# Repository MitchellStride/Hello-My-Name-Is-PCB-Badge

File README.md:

# 🎉 "Hello My Name Is" PCB Badge

This **#Badgelife** PCB was created to test some circuits for future art PCBs.  
It also served as a small project to bring to local hardware meetups. Partial assembly was done at JLCPCB.

## ⚡ Example GIF

---

## 🔧 Features
- Powered by 2× AA Batteries
- Highly compatible with JLCPCB's basic SMT parts
- Raspberry Pi RP2040 microcontroller with dual-core ARM Cortex-M0+
- OLED Screen, RGB LEDs, Buttons
- SAO Connector

---

## ⚠️ v1 Issues
I rushed this project a lot. The schematic was done in a few nights, layout and routing in a few hours with no review. This PCB has a few mistakes. Not planning another spin, but leaving this list here:  

<details>
<summary>Click to expand v1 Issues</summary>

- I saw someone else's design online using an RGB LED running at 3.3V (below spec). I tried to replicate it, and the LEDs were very flaky and worked intermittently. Experiment failed 😢.  
- AA boost converter not yet tested; currently using USB power only.

</details>

---

## 📝 v2 Wishlist
<details>
<summary>Click to expand v2 Todo</summary>

- User LED + Power LED  
- ON/OFF silk on switch  
- Buzzer would be fun  
- 5.1k USB CC1/CC2  
- Planes on battery terminals to prevent lifting  
- Use RPi boost for AA supply instead of boost converter  
  - It’s nice to have 5V for LEDs  
- SAO connector is too big for this little PCB  
- GND probe clip stuffing option  
- Level shifter for RGB LEDs  

</details>

---

*Missing front buttons on this test PCB*

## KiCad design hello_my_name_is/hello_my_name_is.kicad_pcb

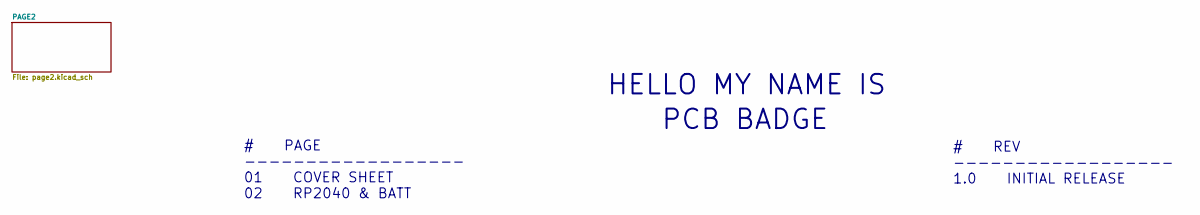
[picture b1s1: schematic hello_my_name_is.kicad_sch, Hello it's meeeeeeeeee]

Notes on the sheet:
# REV ------------------ 1.0 INITIAL RELEASE
HELLO MY NAME IS
PCB BADGE
# PAGE ------------------ 01 COVER SHEET 02 RP2040 & BATT

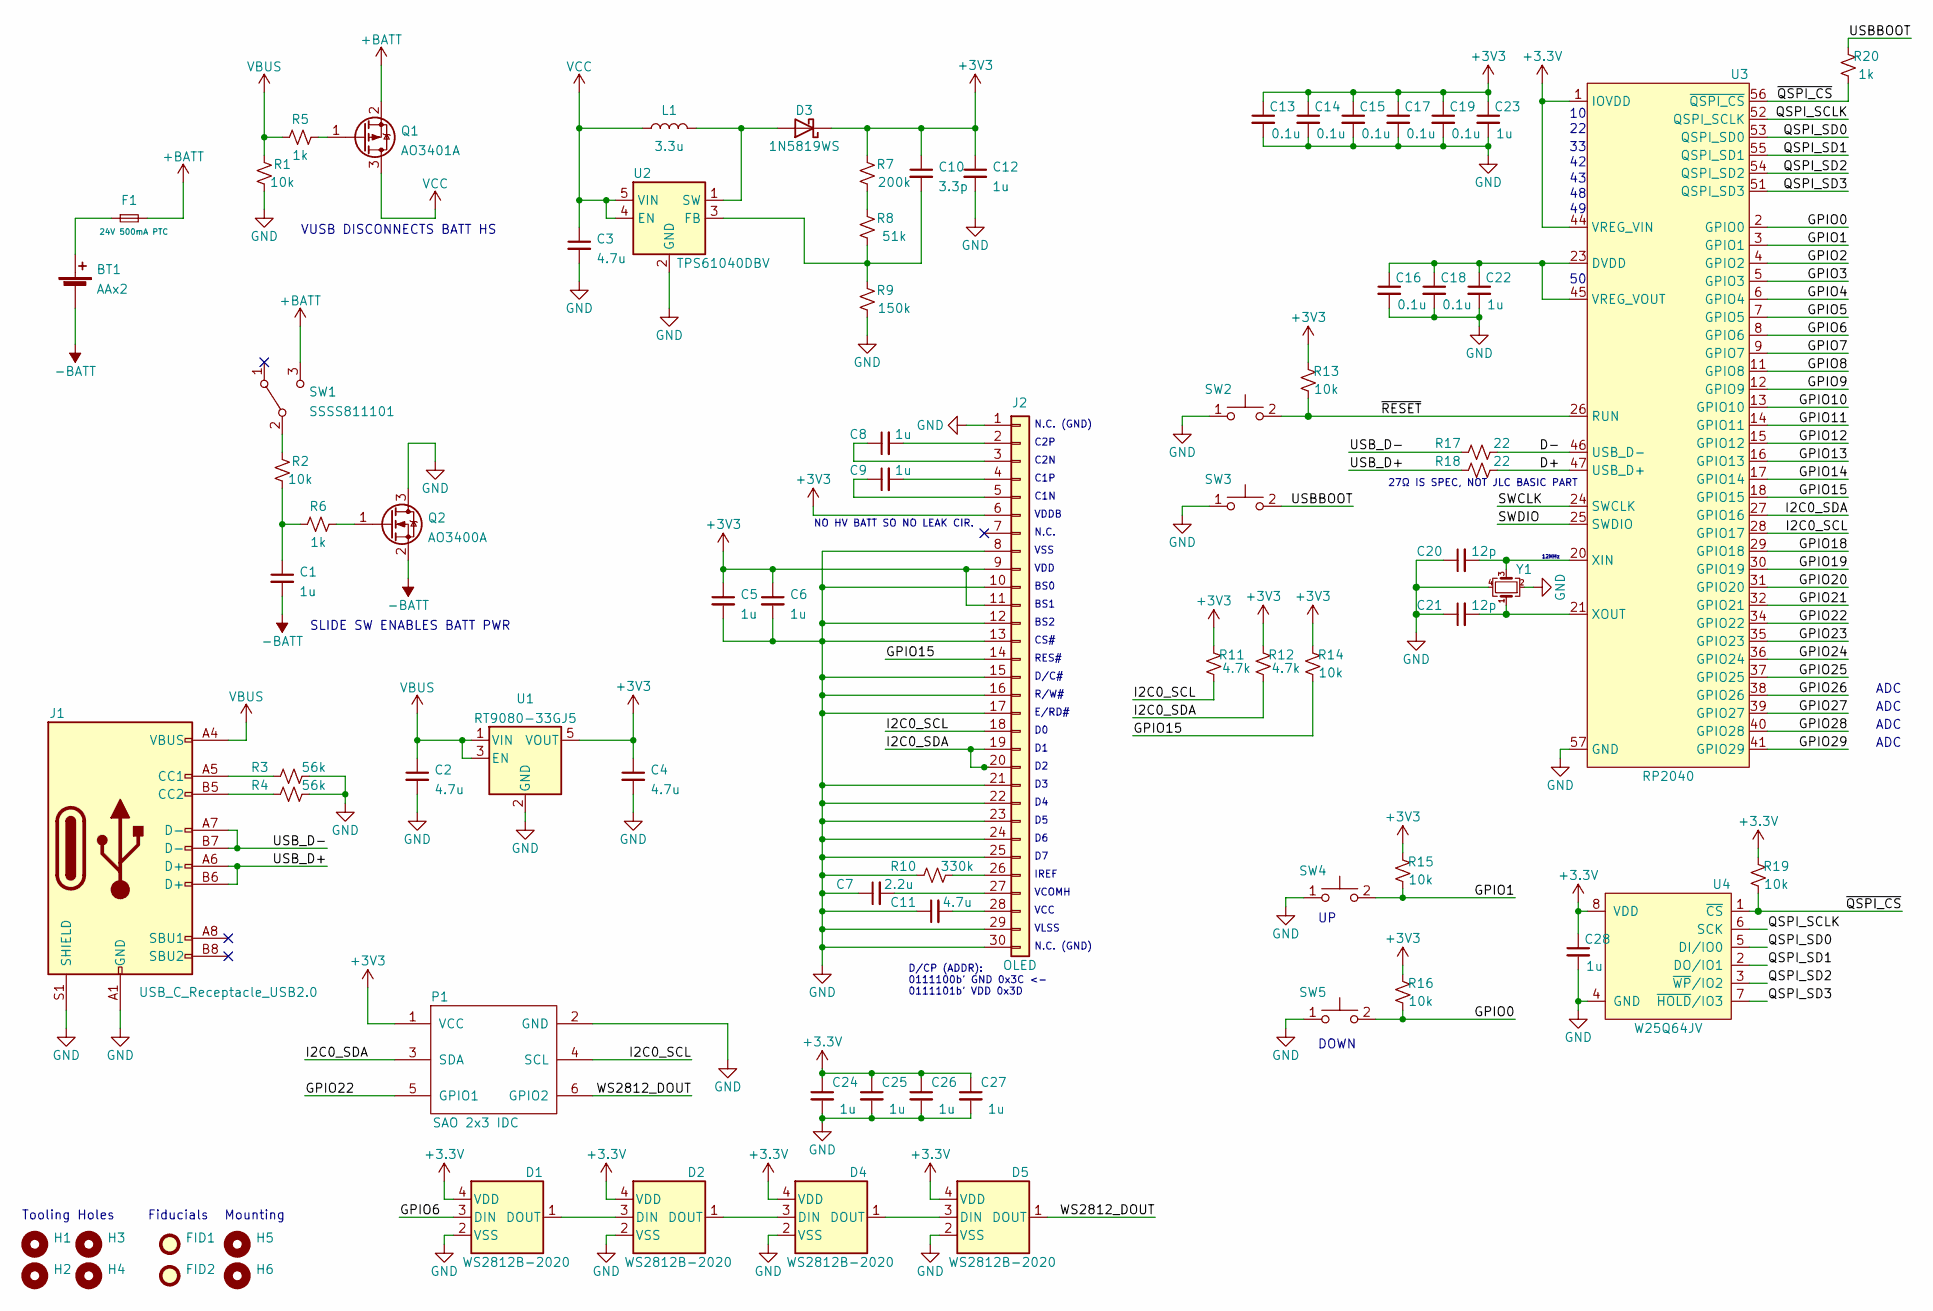
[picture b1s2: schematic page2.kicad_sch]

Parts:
BT1: AAx2; BatteryHolder_MPD_BC2AAPC_2xAA_mod-SMD; digi BC2AAPC
C1, C5, C6, C8, C9, C12, C22, C23, C24, C25, C26, C27, C28: 1u; C_0402_1005Metric; lcsc C52923
C2, C3, C4, C11: 4.7u; C_0402_1005Metric; lcsc C23733
C7: 2.2u; C_0402_1005Metric; lcsc C12530
C10: 3.3p; C_0402_1005Metric; lcsc C1565
C13, C14, C15, C16, C17, C18, C19: 0.1u; C_0402_1005Metric; lcsc C1525
C20, C21: 12p; C_0402_1005Metric; lcsc C1547
D1, D2, D4, D5: WS2812B-2020; lcsc C965555
D3: 1N5819WS; D_SOD-323; lcsc C191023
F1: 24V 500mA PTC; Fuse_0805_2012Metric; lcsc C910822
FID1, FID2: Fiducial; Fiducial_1mm_Mask2mm
H1, H2, H3, H4: Tooling_Hole_JLC; JLC_Tooling_Hole
H5, H6: Tooling_Hole_JLC; MountingHole_3.2mm_M3
J1: USB_C_Receptacle_USB2.0; USB-C-16p; lcsc C167321
J2: OLED; OLED-128O064D; lcsc C2890596
L1: 3.3u; L_Bourns-SRN4018; lcsc C431259
P1: SAO 2x3 IDC; Badgelife-SAOv169-BADGE-2x3; lcsc C11214
Q1: AO3401A; SOT-23; lcsc C15127
Q2: AO3400A; SOT-23; lcsc C20917
R1, R2, R13, R14, R15, R16, R19: 10k; R_0402_1005Metric; lcsc C25744
R3, R4: 56k; R_0402_1005Metric; lcsc C25796
R5, R6, R20: 1k; R_0402_1005Metric; lcsc C11702
R7: 200k; R_0402_1005Metric; lcsc C25764
R8: 51k; R_0402_1005Metric; lcsc C25794
R9: 150k; R_0402_1005Metric; lcsc C25755
R10: 330k; R_0402_1005Metric; lcsc C25778
R11, R12: 4.7k; R_0402_1005Metric; lcsc C25900
R17, R18: 22; R_0402_1005Metric; lcsc C25092
SW1: SSSS811101; lcsc C109335
SW2, SW3, SW4, SW5: TS-1187A-B-A-B; SW_SPST_TL3342; lcsc C318884
U1: RT9080-33GJ5; SOT-23-5; lcsc C841192
U2: TPS61040DBV; SOT-23-5; lcsc C7722
U3: RP2040; QFN-56_EP_7x7_Pitch0.4mm; lcsc C2040
U4: W25Q64JV; SOIC-8W_5.3x5.3mm_P1.27mm; lcsc C179171
Y1: XYDBPCNANF-12MHZ; Crystal_SMD_2520-4Pin_2.5x2.0mm; lcsc C521567

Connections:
+BATT: F1.2, Q1.2 (S), SW1.3 (C)
-BATT: BT1.2 (-), C1.2, Q2.2 (S)
/PAGE2/D+: R18.2, U3.47 (USB_D+)
/PAGE2/D-: R17.2, U3.46 (USB_D-)
/PAGE2/GPIO0: R16.2, SW5.2, U3.2 (GPIO0)
/PAGE2/GPIO1: R15.2, SW4.2, U3.3 (GPIO1)
/PAGE2/GPIO2: U3.4 (GPIO2)
/PAGE2/GPIO3: U3.5 (GPIO3)
/PAGE2/GPIO4: U3.6 (GPIO4)
/PAGE2/GPIO5: U3.7 (GPIO5)
/PAGE2/GPIO6: D1.3 (DIN), U3.8 (GPIO6)
/PAGE2/GPIO7: U3.9 (GPIO7)
/PAGE2/GPIO8: U3.11 (GPIO8)
/PAGE2/GPIO9: U3.12 (GPIO9)
/PAGE2/GPIO10: U3.13 (GPIO10)
/PAGE2/GPIO11: U3.14 (GPIO11)
/PAGE2/GPIO12: U3.15 (GPIO12)
/PAGE2/GPIO13: U3.16 (GPIO13)
/PAGE2/GPIO14: U3.17 (GPIO14)
/PAGE2/GPIO15: J2.14, R14.2, U3.18 (GPIO15)
/PAGE2/GPIO18: U3.29 (GPIO18)
/PAGE2/GPIO19: U3.30 (GPIO19)
/PAGE2/GPIO20: U3.31 (GPIO20)
/PAGE2/GPIO21: U3.32 (GPIO21)
/PAGE2/GPIO22: P1.5 (GPIO1), U3.34 (GPIO22)
/PAGE2/GPIO23: U3.35 (GPIO23)
/PAGE2/GPIO24: U3.36 (GPIO24)
/PAGE2/GPIO25: U3.37 (GPIO25)
/PAGE2/GPIO26: U3.38 (GPIO26)
/PAGE2/GPIO27: U3.39 (GPIO27)
/PAGE2/GPIO28: U3.40 (GPIO28)
/PAGE2/GPIO29: U3.41 (GPIO29)
/PAGE2/I2C0_SCL: J2.18, P1.4 (SCL), R11.2, U3.28 (GPIO17)
/PAGE2/I2C0_SDA: J2.19, J2.20, P1.3 (SDA), R12.2, U3.27 (GPIO16)
/PAGE2/QSPI_SCLK: U3.52 (QSPI_SCLK), U4.6 (SCK)
/PAGE2/QSPI_SD0: U3.53 (QSPI_SD0), U4.5 (DI/IO0)
/PAGE2/QSPI_SD1: U3.55 (QSPI_SD1), U4.2 (DO/IO1)
/PAGE2/QSPI_SD2: U3.54 (QSPI_SD2), U4.3 (~WP/IO2)
/PAGE2/QSPI_SD3: U3.51 (QSPI_SD3), U4.7 (~HOLD/IO3)
/PAGE2/SWCLK: U3.24 (SWCLK)
/PAGE2/SWDIO: U3.25 (SWDIO)
/PAGE2/USBBOOT: R20.1, SW3.2
/PAGE2/USB_D+: J1.A6 (D+), J1.B6 (D+), R18.1
/PAGE2/USB_D-: J1.A7 (D-), J1.B7 (D-), R17.1
/PAGE2/WS2812_DOUT: D5.1 (DOUT), P1.6 (GPIO2)
/PAGE2/~QSPI_CS: R19.2, R20.2, U3.56 (~QSPI_CS), U4.1 (~CS)
/PAGE2/~RESET: R13.2, SW2.2, U3.26 (RUN)
GND: C2.2, C3.2, C4.2, C5.2, C6.2, C7.1, C11.1, C12.2, C13.2, C14.2, C15.2, C16.2, C17.2, C18.2, C19.2, C20.1, C21.1, C22.2, C23.2, C24.2, C25.2, C26.2, C27.2, C28.2, D1.2 (VSS), D2.2 (VSS), D4.2 (VSS), D5.2 (VSS), J1.A1 (GND), J1.A12 (GND), J1.B1 (GND), J1.B12 (GND), J1.S1 (SHIELD), J2.1, J2.8, J2.10, J2.12, J2.13, J2.15, J2.16, J2.17, J2.21, J2.22, J2.23, J2.24, J2.25, J2.29, J2.30, P1.2 (GND), Q2.3 (D), R1.2, R3.2, R4.2, R9.2, R10.1, SW2.1, SW3.1, SW4.1, SW5.1, U1.2 (GND), U2.2 (GND), U3.19 (TESTEN), U3.57 (GND), U4.4 (GND), U4.9 (GND), Y1.2, Y1.4
unnamed: BT1.1 (+), F1.1
unnamed: C1.1, R2.2, R6.1
unnamed: C7.2, J2.27
unnamed: C8.1, J2.3
unnamed: C8.2, J2.2
unnamed: C9.1, J2.5
unnamed: C9.2, J2.4
unnamed: C10.2, R8.2, R9.1, U2.3 (FB)
unnamed: C11.2, J2.28
unnamed: C16.1, C18.1, C22.1, U3.23 (DVDD), U3.45 (VREG_VOUT), U3.50 (DVDD)
unnamed: C20.2, U3.20 (XIN), Y1.3
unnamed: C21.2, U3.21 (XOUT), Y1.1
unnamed: D1.1 (DOUT), D2.3 (DIN)
unnamed: D2.1 (DOUT), D4.3 (DIN)
unnamed: D3.2 (A), L1.2, U2.1 (SW)
unnamed: D4.1 (DOUT), D5.3 (DIN)
unnamed: J1.A5 (CC1), R3.1
unnamed: J1.B5 (CC2), R4.1
unnamed: J2.26, R10.2
unnamed: Q1.1 (G), R5.2
unnamed: Q2.1 (G), R6.2
unnamed: R2.1, SW1.2 (B)
unnamed: R7.2, R8.1
VBUS: C2.1, J1.A4 (VBUS), J1.A9 (VBUS), J1.B4 (VBUS), J1.B9 (VBUS), R1.1, R5.1, U1.1 (VIN), U1.3 (EN)
VCC: C3.1, L1.1, Q1.3 (D), U2.4 (EN), U2.5 (VIN)

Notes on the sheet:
C2N
C1P
D/C#
N.C. (GND)
RES#
Mounting
DOWN
CS#
IREF
VUSB DISCONNECTS BATT HS
BS2
NO HV BATT SO NO LEAK CIR.
D/CP (ADDR): 0111100b' GND 0x3C <- 0111101b' VDD 0x3D
R/W#
ADC
BS1
E/RD#
VCC
VDDB
VDD
27Ω IS SPEC, NOT JLC BASIC PART
Tooling Holes
SLIDE SW ENABLES BATT PWR
VSS
C1N
12MHz
VLSS
Fiducials
N.C.
BS0
VCOMH
C2P

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
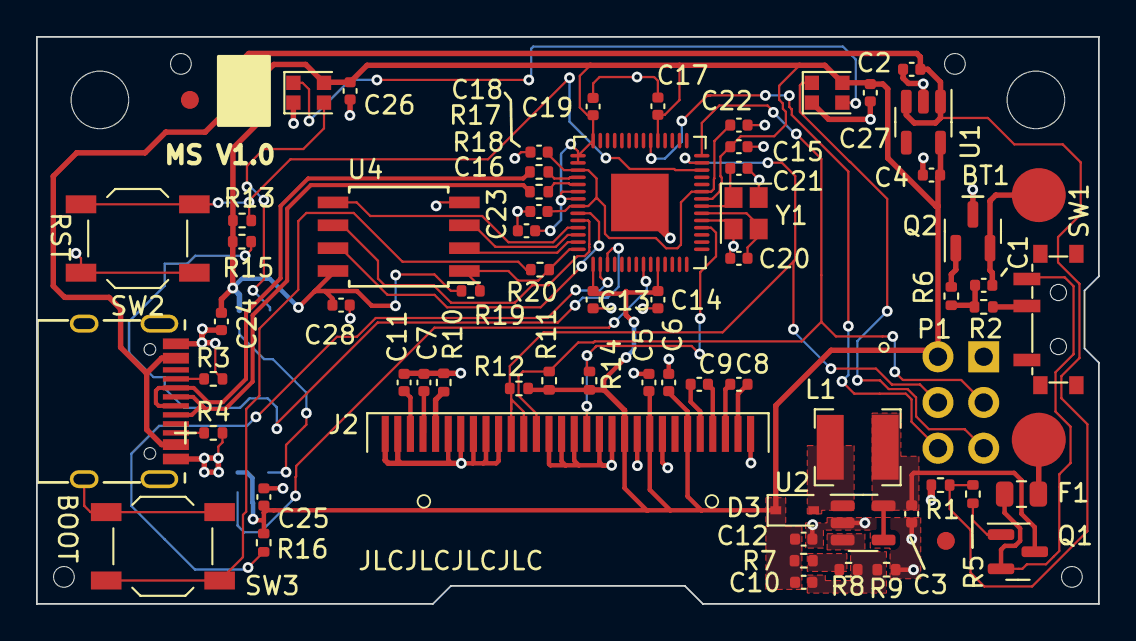
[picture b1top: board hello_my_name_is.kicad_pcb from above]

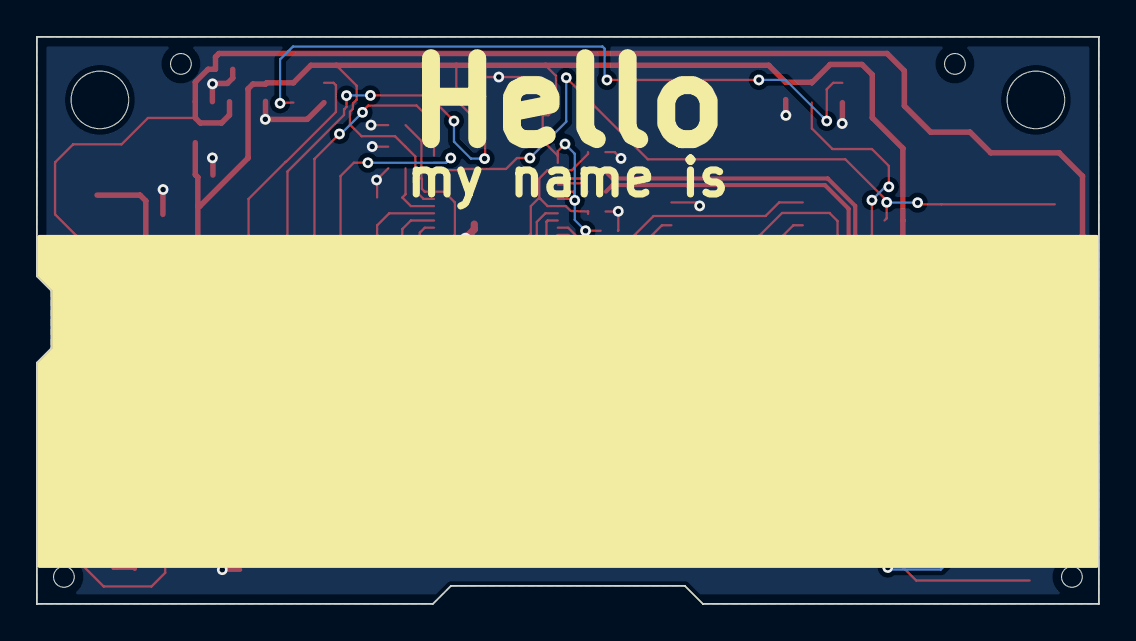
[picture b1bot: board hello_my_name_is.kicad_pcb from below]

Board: 2 copper layers, 59.0 x 31.5 mm, 79 parts (5 on the bottom side), 49 nets.

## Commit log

2022-04-13 first create
2022-04-16 sch update
2022-04-18 sch push before review, some component grouping
2022-04-19 uploading gerbers, going in hot w/ no review
    shotgunned this 2 layer board routing in a few hours... hot garbage!
2022-04-25 created files for firmware tests
2022-04-29 drafted working badge test code for buttons
2022-05-11 sw transfer
2022-05-18 work changes
2022-07-16 added real pics to readme
2022-07-16 add transparent pics
2022-07-16 changed back
2022-07-16 added gif and oled SW
2022-07-17 reached MVP imo
2022-07-17 new gif and test code
2022-07-17 edit
2022-07-17 edit fix
2022-07-17 added headers
2025-12-12 AI readme cleanup
2025-12-12 ai readme 2
